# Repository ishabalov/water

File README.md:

# water
# Simple watering controller based on ESP32
# See kicad-design for schematics & board
# See water_controller for Arduino sketch

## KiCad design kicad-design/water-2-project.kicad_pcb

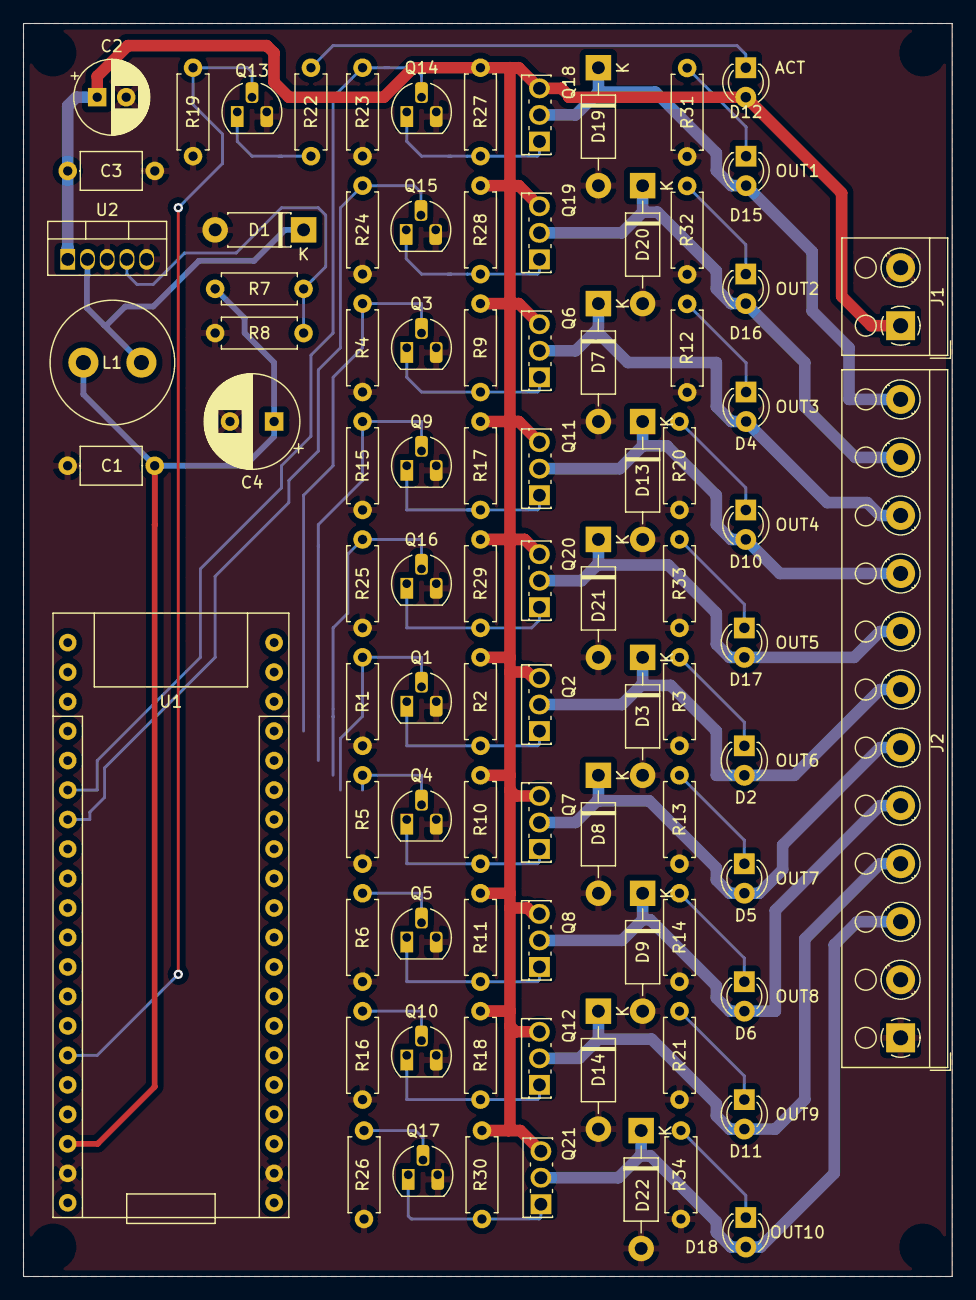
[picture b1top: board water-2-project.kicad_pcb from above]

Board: 2 copper layers, 80.0 x 108.0 mm, 86 parts (0 on the bottom side), 48 nets.

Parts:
C1, C3: 100nF; C_Axial_L5.1mm_D3.1mm_P7.50mm_Horizontal
C2: 100uF; CP_Radial_D6.3mm_P2.50mm
C4: 330uF; CP_Radial_D8.0mm_P3.80mm
D1: UF4004; D_DO-41_SOD81_P7.62mm_Horizontal
D2: OUT6; LED_D3.0mm
D3, D7, D8, D9, D13, D14, D19, D20, D21, D22: 1N4003; D_DO-41_SOD81_P10.16mm_Horizontal
D4: OUT3; LED_D3.0mm
D5: OUT7; LED_D3.0mm
D6: OUT8; LED_D3.0mm
D10: OUT4; LED_D3.0mm
D11: OUT9; LED_D3.0mm
D12: LED ACT; LED_D3.0mm
D15: OUT1; LED_D3.0mm
D16: OUT2; LED_D3.0mm
D17: OUT5; LED_D3.0mm
D18: OUT10; LED_D3.0mm
J1: PW IN; TerminalBlock_RND_205-00001_1x02_P5.00mm_Horizontal
J2: OUTPUT; TerminalBlock_RND_205-00011_1x12_P5.00mm_Horizontal
L1: 330uH; L_Radial_D10.5mm_P5.00mm_Abacron_AISR-01
Q1, Q3, Q4, Q5, Q9, Q10, Q13, Q14, Q15, Q16, Q17: BS170; TO-92L_HandSolder
Q2, Q6, Q7, Q8, Q11, Q12, Q18, Q19, Q20, Q21: SFT1342-D; SIPAK_Vertical
R1, R2, R4, R5, R6, R9, R10, R11, R15, R16, R17, R18, R19, R23, R24, R25, R26, R27, R28, R29, R30: 4.7k; R_Axial_DIN0207_L6.3mm_D2.5mm_P7.62mm_Horizontal
R3, R12, R13, R14, R20, R21, R22, R31, R32, R33, R34: 1k; R_Axial_DIN0207_L6.3mm_D2.5mm_P7.62mm_Horizontal
R7: 1.8k; R_Axial_DIN0207_L6.3mm_D2.5mm_P7.62mm_Horizontal
R8: 1.0k; R_Axial_DIN0207_L6.3mm_D2.5mm_P7.62mm_Horizontal
U1: ESP-32-PICO-KIT; ESP32-PICO-KIT
U2: LM2575BT-ADJ; TO-220-5_Vertical

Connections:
+3V3: C1.1, C4.1, L1.2, R7.1, U1.18
+24V: C2.1, C3.1, D12.2, J1.1, Q2.3, Q6.3, Q7.3, Q8.3, Q11.3, Q12.3, Q18.3, Q19.3, Q20.3, Q21.3, R2.1, R9.1, R10.1, R11.1, R17.1, R18.1, R27.1, R28.1, R29.1, R30.1, U2.1
/IO1: Q14.2, R23.1, U1.6
/IO2: Q15.2, R24.1, U1.7
/IO3: Q3.2, R4.1, U1.26
/IO4: Q9.2, R15.1, U1.27
/IO5: Q16.2, R25.1, U1.28
/IO6: Q1.2, R1.1, U1.29
/IO7: Q4.2, R5.1, U1.30
/IO8: Q5.2, R6.1, U1.31
/IO9: Q10.2, R16.1, U1.34
/IO10: Q17.2, R26.1, U1.35
/IO_ACT: Q13.2, R19.1, U1.15
/OUT1: D15.2, D19.1, J2.12, Q18.2
/OUT2: D16.2, D20.1, J2.11, Q19.2
/OUT3: D4.2, D7.1, J2.10, Q6.2
/OUT4: D10.2, D13.1, J2.9, Q11.2
/OUT5: D17.2, D21.1, J2.8, Q20.2
/OUT6: D2.2, D3.1, J2.7, Q2.2
/OUT7: D5.2, D8.1, J2.6, Q7.2
/OUT8: D6.2, D9.1, J2.5, Q8.2
/OUT9: D11.2, D14.1, J2.4, Q12.2
/OUT10: D18.2, D22.1, J2.3, Q21.2
/PSU_OUT: D1.1, L1.1, U2.2
GND: C1.2, C2.2, C3.2, C4.2, D1.2, D3.2, D7.2, D8.2, D9.2, D13.2, D14.2, D19.2, D20.2, D21.2, D22.2, J1.2, J2.1, J2.2, Q1.3, Q3.3, Q4.3, Q5.3, Q9.3, Q10.3, Q13.3, Q14.3, Q15.3, Q16.3, Q17.3, R1.2, R3.2, R4.2, R5.2, R6.2, R8.2, R12.2, R13.2, R14.2, R15.2, R16.2, R19.2, R20.2, R21.2, R23.2, R24.2, R25.2, R26.2, R31.2, R32.2, R33.2, R34.2, U1.19, U1.39, U2.3, U2.5
unnamed: D2.1, R3.1
unnamed: D4.1, R12.1
unnamed: D5.1, R13.1
unnamed: D6.1, R14.1
unnamed: D10.1, R20.1
unnamed: D11.1, R21.1
unnamed: D12.1, R22.1
unnamed: D15.1, R31.1
unnamed: D16.1, R32.1
unnamed: D17.1, R33.1
unnamed: D18.1, R34.1
unnamed: Q1.1, Q2.1, R2.2
unnamed: Q3.1, Q6.1, R9.2
unnamed: Q4.1, Q7.1, R10.2
unnamed: Q5.1, Q8.1, R11.2
unnamed: Q10.1, Q12.1, R18.2
unnamed: Q9.1, Q11.1, R17.2
unnamed: Q13.1, R22.2
unnamed: Q14.1, Q18.1, R27.2
unnamed: Q15.1, Q19.1, R28.2
unnamed: Q16.1, Q20.1, R29.2
unnamed: Q17.1, Q21.1, R30.2
unnamed: R7.2, R8.1, U2.4

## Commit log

2019-04-10 Added .gitignore Added BMP280 temperrature/pressure sensor
2019-04-10 Added documentation folder
2019-04-10 Project adapted for Eclipse C++ Arduino IDE
2019-04-10 Formatting code.
2019-04-10 Refactoring to c++ style.
2019-04-11 More refactoring
2019-04-11 Continue refactoring
2019-04-22 Added command processor
2019-04-23 Fixing merge conflicts
2019-04-25 Updated design
2019-04-25 Finally we can compile it.
2019-04-26 Fixing array initialization routine
2019-05-10 Keep refactoring
2020-04-28 Updated water controller
